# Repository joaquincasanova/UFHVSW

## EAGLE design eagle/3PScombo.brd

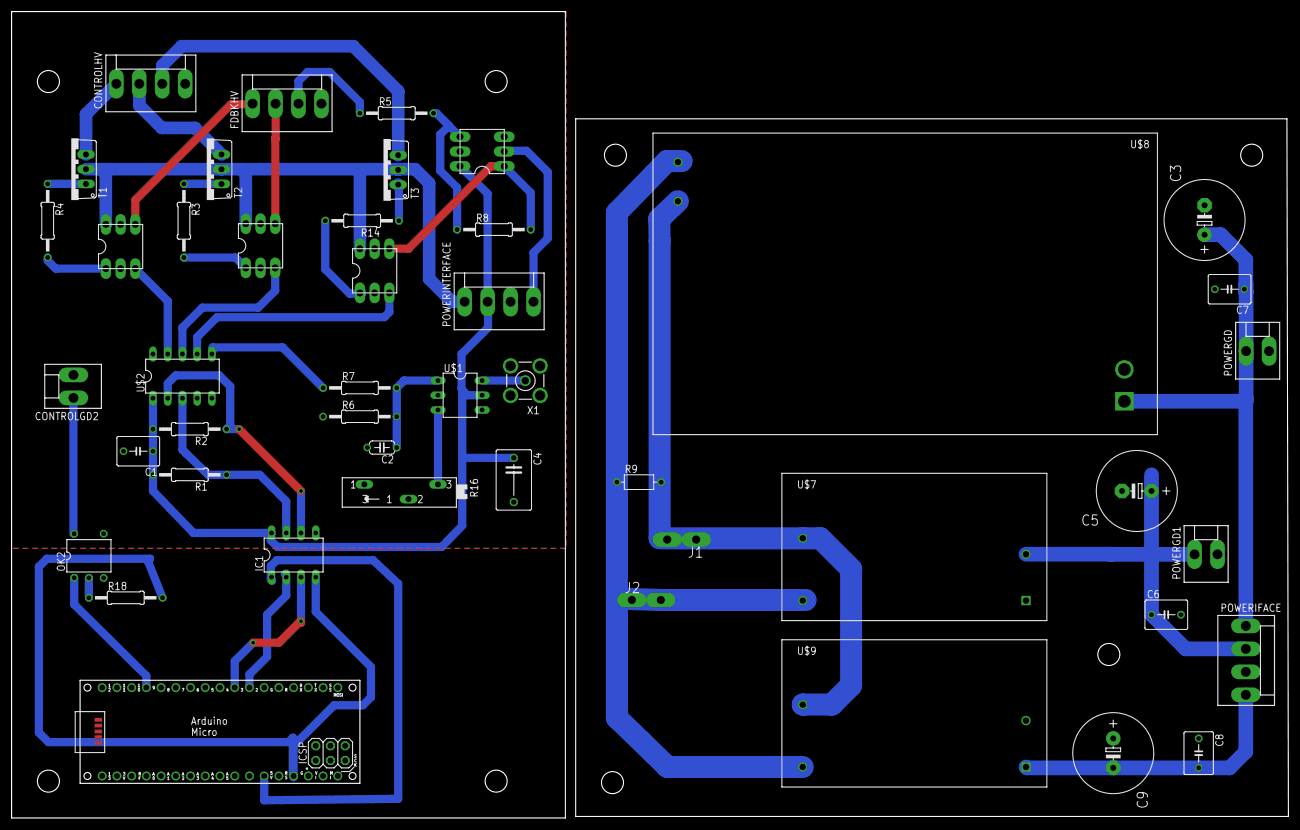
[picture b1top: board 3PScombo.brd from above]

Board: 2 copper layers, 220.2 x 139.1 mm, 46 parts (0 on the bottom side), 40 nets.

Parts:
C1, C6, C7, C8: C050-050X075
C2: 10n; C050-024X044
C3, C5, C9: E5-13
C4: C075-063X106
CONTROLGD2: KK-156-2
CONTROLHV: KK-156-4
FDBKHV: KK-156-4
IC1: ISO1540; DIL08
J1, J2: PIN2F061.100; F061.100
OK2: H11F1; DIL05
PCB1: ARDUINO_MICRO
POWERGD, POWERGD1: KK-156-2
POWERIFACE: KK-156-4
POWERINTERFACE: KK-156-4
R1, R2: 1.5k; 0207/12
R3, R4, R5, R8, R14: 1k; 0207/12
R6: 10k; 0207/12
R7: 40k; 0207/12
R9: VARISTOR-7,5; R-7,5
R16: SP19L
R18: 100; 0207/12
T1, T2, T3: TIP122V; TO220V
U$1: LTC6992; DIL06
U$2: MCP4728DIL; DIL10
U$3, U$4, U$5, U$6: OPA735DIL; DIL6
U$7, U$9: IRM-05-05
U$8: IRM-60-12
X1: BU-SMA-V

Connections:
+12V: POWERINTERFACE.1, T1.2, T2.2, T3.2, U$4.P$6, U$5.P$6, U$6.P$6
+12V1: C3.+, C7.1, POWERGD.1, POWERIFACE.1, U$8.P$1
-5V: POWERINTERFACE.4, U$3.P$2
-5V1: C8.2, C9.-, POWERIFACE.4, U$9.-V
A+5: IC1.1, PCB1.+5V
AGND: IC1.4, PCB1.GND., R18.2
ENSW2: CONTROLGD2.1, OK2.6
GND: C1.2, C2.2, C4.2, CONTROLGD2.2, CONTROLHV.4, FDBKHV.4, IC1.5, OK2.4, POWERINTERFACE.3, R6.1, R16.A, R16.S, U$1.DIV, U$1.GND, U$2.4, U$2.10, U$3.P$3, U$4.P$2, U$5.P$2, U$6.P$2, X1.2, X1.3, X1.4, X1.5
GND1: C3.-, C5.-, C6.2, C7.2, C8.1, C9.+, POWERGD.2, POWERGD1.2, POWERIFACE.3, U$7.-V, U$8.P$2, U$9.+V
unnamed: R7.1, U$2.6
unnamed: C2.1, R6.2, R7.2, U$1.MOD
unnamed: R4.1, T1.1
unnamed: CONTROLHV.1, T1.3
unnamed: CONTROLHV.3, T3.3
unnamed: FDBKHV.2, U$5.P$4
unnamed: OK2.2, R18.1
unnamed: FDBKHV.1, U$6.P$4
unnamed: FDBKHV.3, R5.1
unnamed: R3.2, U$5.P$1
unnamed: CONTROLHV.2, T2.3
unnamed: R16.E, U$1.SET
unnamed: U$1.OUT, X1.1
unnamed: R8.2, U$3.P$1, U$4.P$4
unnamed: R14.1, T3.1
unnamed: U$2.9, U$6.P$3
unnamed: U$2.8, U$5.P$3
unnamed: U$2.7, U$4.P$3
unnamed: R4.2, U$6.P$1
unnamed: R3.1, T2.1
unnamed: R14.2, U$4.P$1
unnamed: R5.2, R8.1, U$3.P$4
unnamed: J1.A1, J1.A2, R9.2, U$7.ACN, U$8.P$4, U$9.ACN
unnamed: J2.A1, J2.A2, R9.1, U$7.ACL, U$8.P$3, U$9.ACL
PWM9: OK2.1, PCB1.D9
SCL: IC1.3, PCB1.D3
SCL_OUT: IC1.6, R2.1, U$2.2
SDA: IC1.2, PCB1.D2
SDA_OUT: IC1.7, R1.1, U$2.3
VCC: C1.1, C4.1, IC1.8, POWERINTERFACE.2, R1.2, R2.2, U$1.VCC, U$2.1, U$3.P$6
VCC1: C5.+, C6.1, POWERGD1.1, POWERIFACE.2, U$7.+V

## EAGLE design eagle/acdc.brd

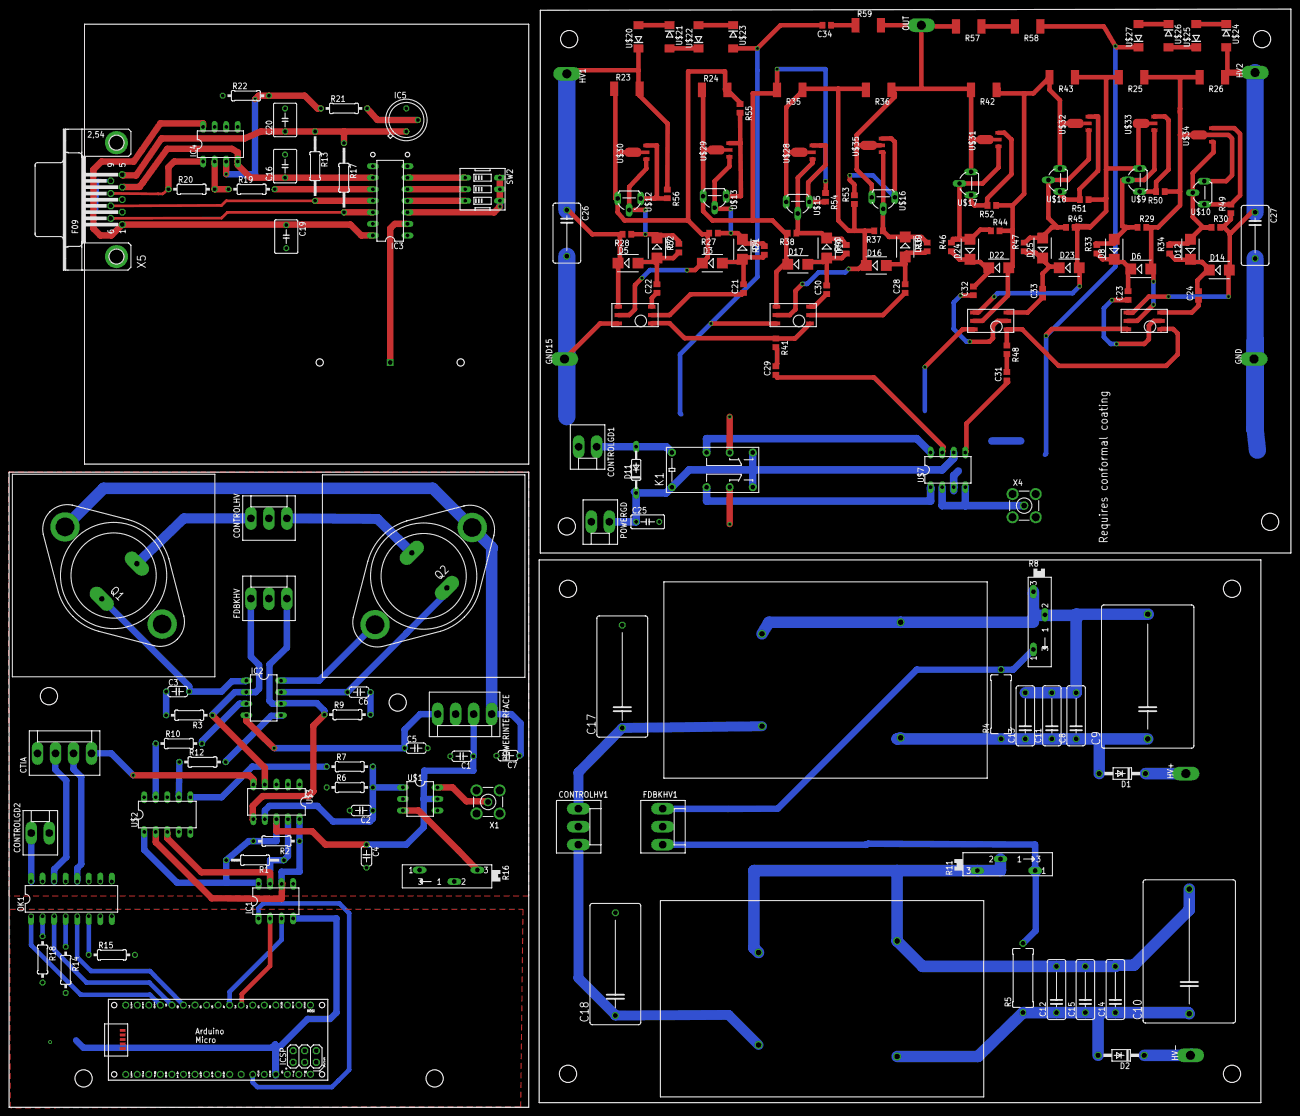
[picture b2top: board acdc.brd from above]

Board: 2 copper layers, 281.9 x 241.6 mm, 177 parts (1 on the bottom side), 122 nets.

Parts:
C1, C2, C3, C4, C5, C6, C7: 10n; C050-024X044
C8, C12: .01u; C102-043X133
C9, C10: 1u; C275-205X316
C11, C14: 1n; C102-043X133
C13, C15: 10p; C102-043X133
C16, C19, C20: 10n; C050-050X075
C17, C18: .1u; C225-113X268
C21, C22, C23, C24, C28, C29, C30, C31, C32, C33: 1u; C0805
C25: 10n; C050-030X075
C26, C27: 10p; C102-064X133
C34: 10n; C0805
CONTROLGD1, CONTROLGD2: KK-156-2
CONTROLHV, CONTROLHV1: KK-156-3
CTIA: KK-156-4
D1, D2: 1N4004; DO41-10
D3, D5, D6, D14, D16, D17, D22, D23: 1SMB5918BT3G; SMB
D4, D7, D8, D12, D18, D19, D24, D25: SMB
D11: 1N4148DO35-10; DO35-10
FDBKHV, FDBKHV1: KK-156-3
GND, GND15: TPPAD1-20Y; P1-20Y
HV1, HV2: TPPAD1-20Y; P1-20Y
HV+: TPPAD1-20Y; P1-20Y
HV-: TPPAD1-20Y; P1-20Y
IC1: ISO1540; DIL08
IC2, IC4: LT1352PA; DIL08
IC3: IVC102UADAPTOR; DIL14
IC5: AD580H; TO39
K1: G5V-2
OK1: PS2501"; DIL16
OUT: TPPAD1-20Y; P1-20Y
PCB1: ARDUINO_MICRO
POWERGD: KK-156-2
POWERINTERFACE: KK-156-4
Q1, Q2: 2N3055; TO3
R1: 10k; 0207/12
R2, R3, R6, R9, R10, R12, R19, R22: 10k; 0207/10
R4, R5: 2M; P0613/15
R7: 40k; 0207/10
R8, R11: SP19L
R13, R17: 10k; 0207/15
R14, R15, R18: 100; 0207/10
R16: 100k; SP19L
R20, R21: 1.5M; 0207/10
R23, R24, R25, R26, R35, R36, R42, R43, R57, R58, R59: 10M; R2512
R27, R28, R29, R30, R37, R38, R44, R45: 100k; R0805
R31, R32, R33, R34, R39, R40, R41, R46, R47, R48: 10; R0805
R49, R50, R51, R52: 6.67; R0805
R53, R54, R55, R56: 1.25; R0805
SW2: EDG-03
U$1: LTC6992; DIL06
U$2: MCP4728DIL; DIL10
U$3: ADS1015DIL; DIL10
U$4, U$5: EMCO-F104PIN; EMCO-F
U$6: CTIA
U$7: UCC27425; DIL08
U$8, U$11, U$14, U$19: DA-2320SMD6; SMD6
U$9, U$10, U$17, U$18: VN0550L; TO92L
U$12, U$13, U$15, U$16: VP0550L; TO92L
U$20, U$21, U$22, U$23, U$24, U$25, U$26, U$27: SMBJ170D-M3/H; DO214AA
U$28, U$29, U$30, U$35: VP2450; SOT89-BCE
U$31, U$32, U$33, U$34: VN2450; SOT89-BCE
X1, X4: BU-SMA-V
X5: F09HP

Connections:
+5V: C20.1, IC5.1, R13.1, R17.1, X5.5
+15V: C7.1, IC2.8, POWERINTERFACE.1, Q1.C, Q1.C/, Q2.C, Q2.C/
+15V1: C19.1, IC3.14, IC4.8, X5.1
+15V2: C25.1, D11.C, K1.1, K1.8, K1.9, POWERGD.1, U$7.6
-15V: C5.1, IC2.4, POWERINTERFACE.4
-15V1: C16.1, IC3.9, IC4.4, X5.4
A+5: IC1.1, PCB1.+5V
AGND: IC1.4, PCB1.GND., R14.2, R15.2, R18.2
CTIA: CTIA.4, U$3.5
D7: OK1.5, PCB1.D7
D8: OK1.3, PCB1.D8
ENSW: CONTROLGD1.1, D11.A, K1.16
ENSW2: CONTROLGD2.1, OK1.16
GND: C1.2, C2.2, C4.2, C5.2, C7.2, CONTROLGD2.2, CONTROLHV.2, CTIA.1, FDBKHV.2, IC1.5, OK1.11, OK1.13, OK1.15, POWERINTERFACE.3, R6.1, R16.A, R16.S, U$1.DIV, U$1.GND, U$2.4, U$2.10, U$3.1, U$3.3, X1.2, X1.3, X1.4, X1.5
GND1: C8.2, C9.2, C10.2, C11.2, C12.2, C13.2, C14.2, C15.2, C17.2, C18.2, CONTROLHV1.2, FDBKHV1.2, R8.E, R8.S, R11.E, R11.S, U$4.P$2, U$4.P$4, U$5.P$2, U$5.P$4
GND2: C16.2, C19.2, C20.2, IC3.1, IC3.13, IC5.3, R22.1, X5.2, X5.3, X5.9
GND3: C25.2, C26.2, C27.2, C34.2, CONTROLGD1.2, GND.TP, GND15.TP, K1.6, K1.11, POWERGD.2, R58.1, U$7.3, U$8.P$6, U$11.P$6, U$14.P$6, U$19.P$6, U$23.A, U$27.C, X4.2, X4.3, X4.4, X4.5
unnamed: R7.1, U$2.6
unnamed: OK1.4, R14.1
unnamed: C3.1, R3.2
unnamed: CONTROLHV.1, Q1.E
unnamed: CONTROLHV.3, Q2.E
unnamed: OK1.6, R15.1
unnamed: OK1.2, R18.1
unnamed: C8.1, C9.1, C11.1, C13.1, D1.A, R4.1, U$4.P$3
unnamed: C10.1, C12.1, C14.1, C15.1, D2.A, R5.1, U$5.P$3
unnamed: FDBKHV1.1, R4.2, R8.A
unnamed: FDBKHV1.3, R5.2, R11.A
unnamed: R16.E, U$1.SET
unnamed: U$1.OUT, X1.1
unnamed: D1.C, HV+.TP
unnamed: C17.1, CONTROLHV1.1, U$4.P$1
unnamed: IC2.3, R10.2
unnamed: C18.1, CONTROLHV1.3, U$5.P$1
unnamed: IC2.5, R12.2
unnamed: C3.2, IC2.1, Q1.B
unnamed: C6.1, R9.2
unnamed: C6.2, IC2.7, Q2.B
unnamed: D2.C, HV-.TP
unnamed: R10.1, U$2.9
unnamed: R12.1, U$2.7
unnamed: IC3.6, SW2.1
unnamed: IC3.5, SW2.2
unnamed: IC3.4, SW2.3
unnamed: IC3.3, SW2.4, SW2.5, SW2.6
unnamed: IC3.10, R19.2
unnamed: IC4.2, R19.1, R20.2
unnamed: IC4.3, R21.1, R22.2
unnamed: IC5.2, R21.2
unnamed: U$7.2, U$7.4, X4.1
unnamed: C29.1, U$7.7
unnamed: C31.1, U$7.5
unnamed: K1.4, U$7.1
unnamed: K1.13, U$7.8
unnamed: C21.1, U$8.P$2
unnamed: C22.1, U$8.P$3
unnamed: C23.1, U$11.P$2
unnamed: C24.1, U$11.P$3
unnamed: C23.2, D6.C, D8.C, R33.1
unnamed: C24.2, D12.C, D14.C, R34.1
unnamed: C22.2, D5.A, D7.A, R32.1
unnamed: C26.1, D5.C, HV1.TP, R23.2, R28.2, R56.1, U$8.P$4, U$20.C
unnamed: D6.A, R25.1, R26.2, R29.2, R50.1, U$10.1, U$11.P$5, U$34.C, U$34.C@1
unnamed: D3.C, R23.1, R24.2, R27.2, R55.1, U$8.P$5, U$12.1, U$30.C, U$30.C@1
unnamed: D4.C, R27.1, R31.2, U$13.2, U$29.B
unnamed: C21.2, D3.A, D4.A, R31.1
unnamed: D12.A, R30.1, R34.2, U$10.2, U$34.B
unnamed: D7.C, R28.1, R32.2, U$12.2, U$30.B
unnamed: C27.1, D14.A, HV2.TP, R26.1, R30.2, R49.1, U$11.P$4, U$24.A
unnamed: C28.1, U$14.P$2
unnamed: C30.1, U$14.P$3
unnamed: C30.2, D17.A, D19.A, R40.1
unnamed: D16.C, R35.1, R36.2, R37.2, R53.1, U$14.P$5, U$15.1, U$28.C, U$28.C@1
unnamed: D18.C, R37.1, R39.2, U$16.2, U$35.B
unnamed: C28.2, D16.A, D18.A, R39.1
unnamed: D19.C, R38.1, R40.2, U$15.2, U$28.B
unnamed: R41.1, U$8.P$1, U$14.P$1
unnamed: C29.2, R41.2
unnamed: C32.1, U$19.P$2
unnamed: C33.1, U$19.P$3
unnamed: C32.2, D22.C, D24.C, R46.1
unnamed: C33.2, D23.C, D25.C, R47.1
unnamed: D22.A, R42.1, R43.2, R44.2, R52.1, U$18.1, U$19.P$5, U$32.C, U$32.C@1
unnamed: D25.A, R45.1, R47.2, U$18.2, U$32.B
unnamed: R48.1, U$11.P$1, U$19.P$1
unnamed: C31.2, R48.2
unnamed: D24.A, R44.1, R46.2, U$17.2, U$31.B
unnamed: D23.A, R25.2, R43.1, R45.2, R51.1, U$9.1, U$19.P$4, U$33.C, U$33.C@1
unnamed: OUT.TP, R36.1, R42.2, R57.2, R59.2, U$16.1, U$17.1, U$31.C, U$31.C@1, U$35.C, U$35.C@1
unnamed: D17.C, R24.1, R35.2, R38.2, R54.1, U$13.1, U$14.P$4, U$29.C, U$29.C@1
unnamed: R49.2, U$10.3, U$34.E
unnamed: R50.2, U$9.3, U$33.E
unnamed: R51.2, U$18.3, U$32.E
unnamed: R52.2, U$17.3, U$31.E
unnamed: R56.2, U$12.3, U$30.E
unnamed: R55.2, U$13.3, U$29.E
unnamed: R53.2, U$16.3, U$35.E
unnamed: R54.2, U$15.3, U$28.E
unnamed: R57.1, R58.2
unnamed: C34.1, R59.1
unnamed: U$20.A, U$21.C
unnamed: U$21.A, U$22.C
unnamed: U$22.A, U$23.C
unnamed: U$24.C, U$25.A
unnamed: U$25.C, U$26.A
unnamed: U$26.C, U$27.A
unnamed: D8.A, R29.1, R33.2, U$9.2, U$33.B
PWM9: OK1.1, PCB1.D9
RDBK1: FDBKHV.1, IC2.2, R3.1, U$3.4
RDBK3: FDBKHV.3, IC2.6, R9.1, U$3.6
RDBK4: C2.1, R6.2, R7.2, U$1.MOD, U$3.7
RESET: CTIA.3, OK1.12
RESET1: IC3.12, R17.2, X5.6
SAMPLE: CTIA.2, OK1.14
SAMPLE1: IC3.11, R13.2, X5.7
SCL: IC1.3, PCB1.D3
SCL_OUT: IC1.6, R2.1, U$2.2, U$3.10
SDA: IC1.2, PCB1.D2
SDA_OUT: IC1.7, R1.1, U$2.3, U$3.9
VCC: C1.1, C4.1, IC1.8, POWERINTERFACE.2, R1.2, R2.2, U$1.VCC, U$2.1, U$3.8
VIN: IC3.2, U$6.P$1
VOUT: IC4.1, R20.1, X5.8

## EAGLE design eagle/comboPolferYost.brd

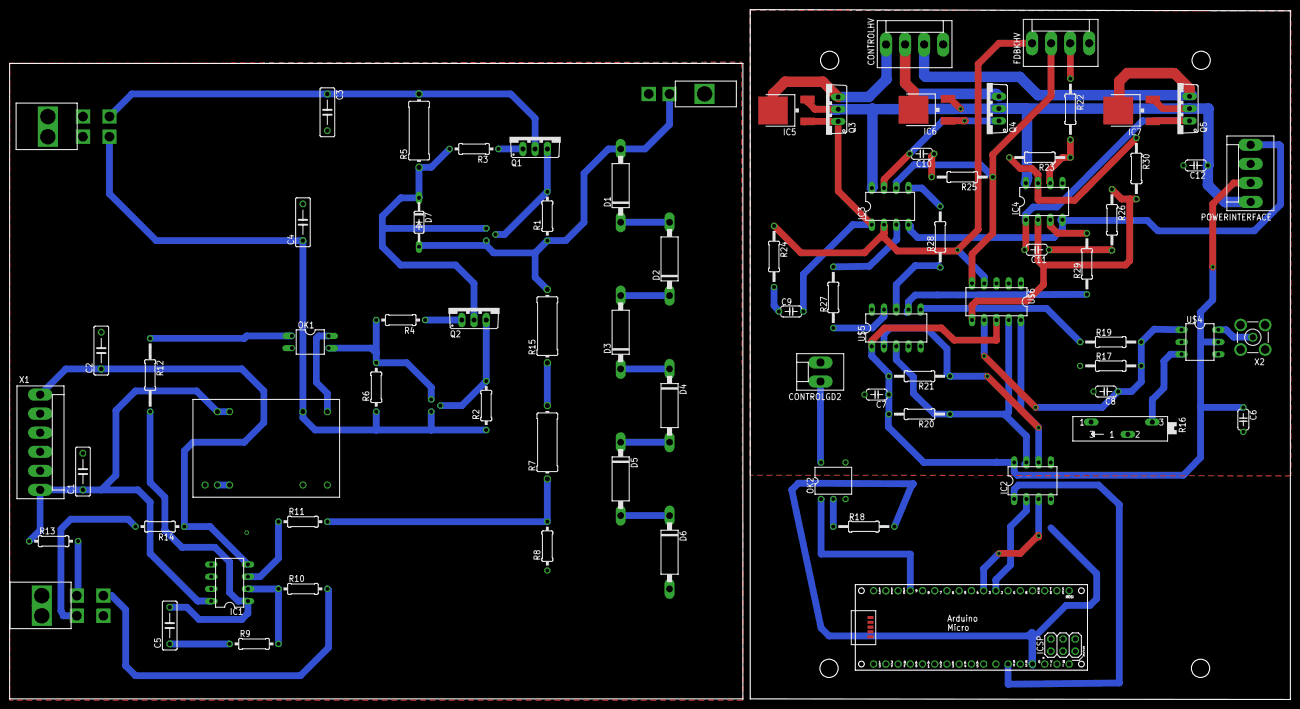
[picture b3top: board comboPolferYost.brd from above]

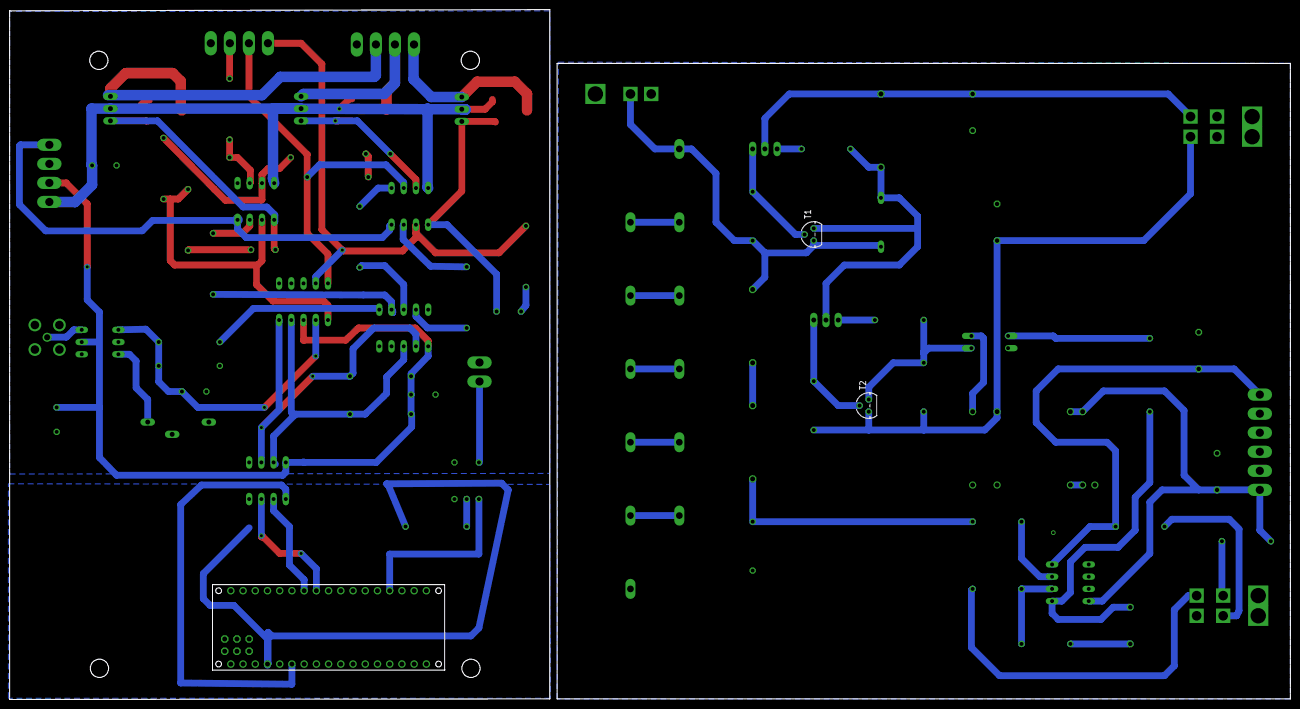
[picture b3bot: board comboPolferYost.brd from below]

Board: 2 copper layers, 266.2 x 143.4 mm, 79 parts (2 on the bottom side), 67 nets.

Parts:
C1, C2, C3, C4, C5: 10n; C075-032X103
C6, C7, C8, C9, C10, C11, C12: 10n; C050-024X044
CONTROLGD2: KK-156-2
CONTROLHV: KK-156-4
D1, D2, D3, D4, D5, D6: P6KEXX; CB417-15
D7: 1N4148DO35-10; DO35-10
DC1: NCS
FDBKHV: KK-156-4
IC1, IC3, IC4: LT1352PA; DIL08
IC2: ISO1540; DIL08
IC5, IC6, IC7: LM317MABDT; DPACK
OK1: PC817; DIL04
OK2: H11F1; DIL05
PCB1: ARDUINO_MICRO
POWERINTERFACE: KK-156-4
Q1, Q2: TO220BV
Q3, Q4, Q5: TIP122V; TO220V
R1, R2: 65; 0207/10
R3, R4: 100; 0207/10
R5, R7, R15: 1M; 0414/15
R6: 100k; 0207/10
R8: 50k; 0207/10
R9, R10, R11: 10k; 0207/10
R12: 250; 0207/15
R13, R14: 20k; 0207/10
R16: 100k; SP19L
R17, R24, R25, R26, R27, R28, R29, R30: 10k; 0207/12
R18: 100; 0207/12
R19: 40k; 0207/12
R20, R21: 1.5k; 0207/12
R22, R23: 20k; 0207/12
T1, T2: 2N3904; TO92
U$1, U$2: 5569-4; 5669-4
U$3: 5569-2
U$4: LTC6992; DIL06
U$5: MCP4728DIL; DIL10
U$6: ADS1015DIL; DIL10
X1: KK-156-6
X2: BU-SMA-V

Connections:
+5V: X1.4, X1.5
+12V: C12.1, IC3.8, IC4.8, IC5.3, IC6.3, IC7.3, POWERINTERFACE.1, Q3.2, Q4.2, Q5.2
+15V: C1.1, DC1.P$8, DC1.P$9, IC1.8, R13.1, X1.6
-5V: IC3.4, IC4.4, POWERINTERFACE.4
-15V: C2.1, IC1.4, R14.1, X1.1
A+5: IC2.1, PCB1.+5V
AGND: IC2.4, PCB1.GND., R18.2
ENSW2: CONTROLGD2.1, OK2.6
GND: C1.2, C2.2, C3.2, C4.2, D6.A, DC1.P$2, DC1.P$3, OK1.2, R8.1, U$2.P$1, U$2.P$2, U$3.P$2, X1.2, X1.3
GND1: C6.2, C7.2, C8.2, C12.2, CONTROLGD2.2, CONTROLHV.4, FDBKHV.4, IC2.5, IC4.5, OK2.4, POWERINTERFACE.3, R16.A, R16.S, R17.1, U$4.DIV, U$4.GND, U$5.4, U$5.10, U$6.1, U$6.3, X2.2, X2.3, X2.4, X2.5
unnamed: D1.C, D2.A
unnamed: D2.C, D3.A
unnamed: D3.C, D4.C
unnamed: D4.A, D5.C
unnamed: D5.A, D6.C
unnamed: Q1.G, R3.1
unnamed: D7.C, Q2.D, R3.2, R5.1, T1.1
unnamed: Q1.S, R1.2, T1.2
unnamed: R13.2, U$1.P$2
unnamed: D1.A, D7.A, R1.1, R15.2, T1.3, U$3.P$1
unnamed: Q2.G, R4.1
unnamed: OK1.3, R4.2, R6.2, T2.1
unnamed: R10.2, U$1.P$4
unnamed: Q2.S, R2.2, T2.2
unnamed: DC1.P$6, OK1.4
unnamed: C5.1, R9.1
unnamed: IC1.2, R9.2, R10.1
unnamed: C5.2, IC1.1, R12.2
unnamed: IC1.3, R11.1
unnamed: R7.1, R8.2, R11.2
unnamed: R16.E, U$4.SET
unnamed: R7.2, R15.1
unnamed: R14.2, U$1.P$1
unnamed: OK1.1, R12.1
unnamed: U$4.OUT, X2.1
unnamed: IC4.7, R23.2, R30.1
unnamed: IC3.5, R28.2
unnamed: IC4.3, R29.2
unnamed: R19.1, U$5.6
unnamed: C9.2, IC3.1, IC5.1, Q3.1
unnamed: CONTROLHV.1, IC5.4, Q3.3
unnamed: C10.2, IC3.7, IC6.1, Q4.1
unnamed: FDBKHV.3, R22.1
unnamed: IC4.6, R22.2, R23.1
unnamed: C11.2, IC4.1, IC7.1, Q5.1
unnamed: OK2.2, R18.1
unnamed: C9.1, R24.2
unnamed: C10.1, R25.2
unnamed: C11.1, R26.2
unnamed: IC3.3, R27.2
unnamed: R27.1, U$5.9
unnamed: R29.1, U$5.7
unnamed: R28.1, U$5.8
unnamed: CONTROLHV.3, IC7.4, Q5.3
unnamed: CONTROLHV.2, IC6.4, Q4.3
PWM9: OK2.1, PCB1.D9
RDBK1: FDBKHV.1, IC3.2, R24.1, U$6.4
RDBK2: FDBKHV.2, IC3.6, R25.1, U$6.5
RDBK3: IC4.2, R26.1, R30.2, U$6.6
RDBK4: C8.1, R17.2, R19.2, U$4.MOD, U$6.7
SCL: IC2.3, PCB1.D3
SCL_OUT: IC2.6, R21.1, U$5.2, U$6.10
SDA: IC2.2, PCB1.D2
SDA_OUT: IC2.7, R20.1, U$5.3, U$6.9
V+: C3.1, Q1.D, R5.2, U$2.P$4
V-: C4.1, DC1.P$7, R2.1, R6.1, T2.3, U$2.P$3
VCC: C6.1, C7.1, IC2.8, POWERINTERFACE.2, R20.2, R21.2, U$4.VCC, U$5.1, U$6.8

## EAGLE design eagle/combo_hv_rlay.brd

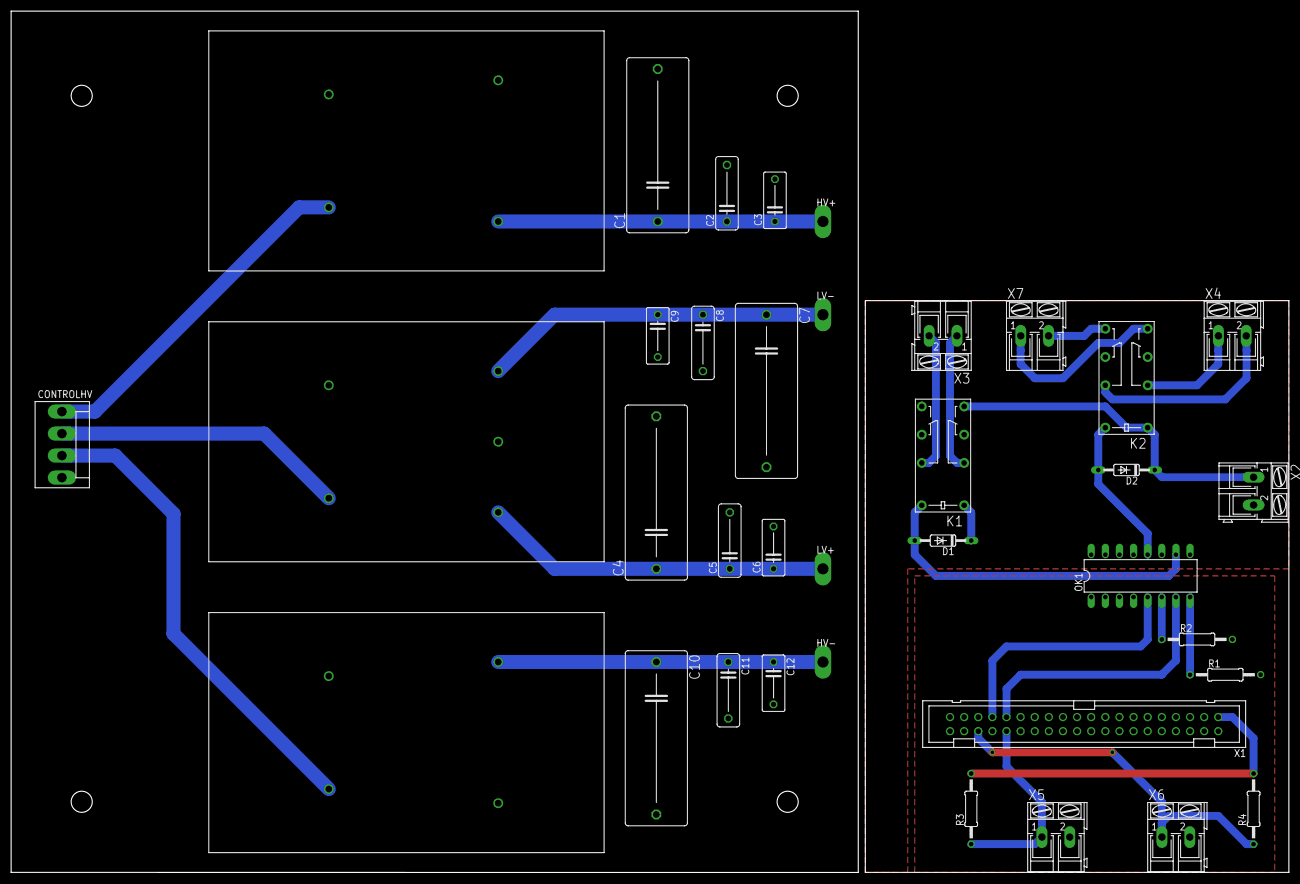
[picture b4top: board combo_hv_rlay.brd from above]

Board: 2 copper layers, 229.9 x 155.0 mm, 36 parts (0 on the bottom side), 28 nets.

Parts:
C1, C4, C7, C10: 1u; C275-113X316
C2, C5, C8, C11: .1u; C102-043X133
C3, C6, C9, C12: .01u; C075-042X103
CONTROLHV: KK-156-4
D1, D2: 1N4148DO35-10; DO35-10
HV+: TPPAD1-20Y; P1-20Y
HV-: TPPAD1-20Y; P1-20Y
K1, K2: G5V-2
LV+: TPPAD1-20Y; P1-20Y
LV-: TPPAD1-20Y; P1-20Y
OK1: PS2501"; DIL16
R1, R2: 200; 0207/12
R3, R4: 1k; 0207/12
U$1, U$3: EMCO-F104PIN; EMCO-F
U$2: EMCO-F20CT; EMCO-F*CT
X1: 2540-; PAK100/2500-40
X2, X3, X4, X5, X6, X7: AK300/2

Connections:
+3V3: R3.2, R4.2, X1.1, X1.17
+5V: X1.2, X1.4
+24V: D1.C, D2.C, K1.1, K1.8, K2.1, X2.1
GND: C1.2, C2.2, C3.2, C4.2, C5.2, C6.2, C7.2, C8.2, C9.2, C10.2, C11.2, C12.2, CONTROLHV.4, U$1.P$2, U$1.P$4, U$2.P$2, U$2.P$5, U$3.P$2, U$3.P$3
GND1: R1.2, R2.2, X1.6, X1.9, X1.14, X1.20, X1.25, X1.30, X1.34, X1.39, X5.2, X6.2
GND2: K1.9, OK1.9, OK1.11, X2.2
GPIO6: OK1.7, X1.31
GPIO13: OK1.5, X1.33
unnamed: C1.1, C2.1, C3.1, HV+.TP, U$1.P$3
unnamed: C10.1, C11.1, C12.1, HV-.TP, U$3.P$4
unnamed: OK1.8, R1.1
unnamed: OK1.6, R2.1
unnamed: C4.1, C5.1, C6.1, LV+.TP, U$2.P$3
unnamed: C7.1, C8.1, C9.1, LV-.TP, U$2.P$4
unnamed: R3.1, X1.32, X5.1
unnamed: D1.A, K1.16, OK1.10
unnamed: D2.A, K2.16, OK1.12
unnamed: K1.4, X3.1
unnamed: K1.13, X3.2
unnamed: X1.36, X6.1
unnamed: R4.1, X6.1
unnamed: K2.13, X4.2
unnamed: K2.4, X4.1
unnamed: K2.8, X7.1
unnamed: K2.9, X7.2
VREG1: CONTROLHV.1, U$1.P$1
VREG2: CONTROLHV.2, U$2.P$1
VREG3: CONTROLHV.3, U$3.P$1

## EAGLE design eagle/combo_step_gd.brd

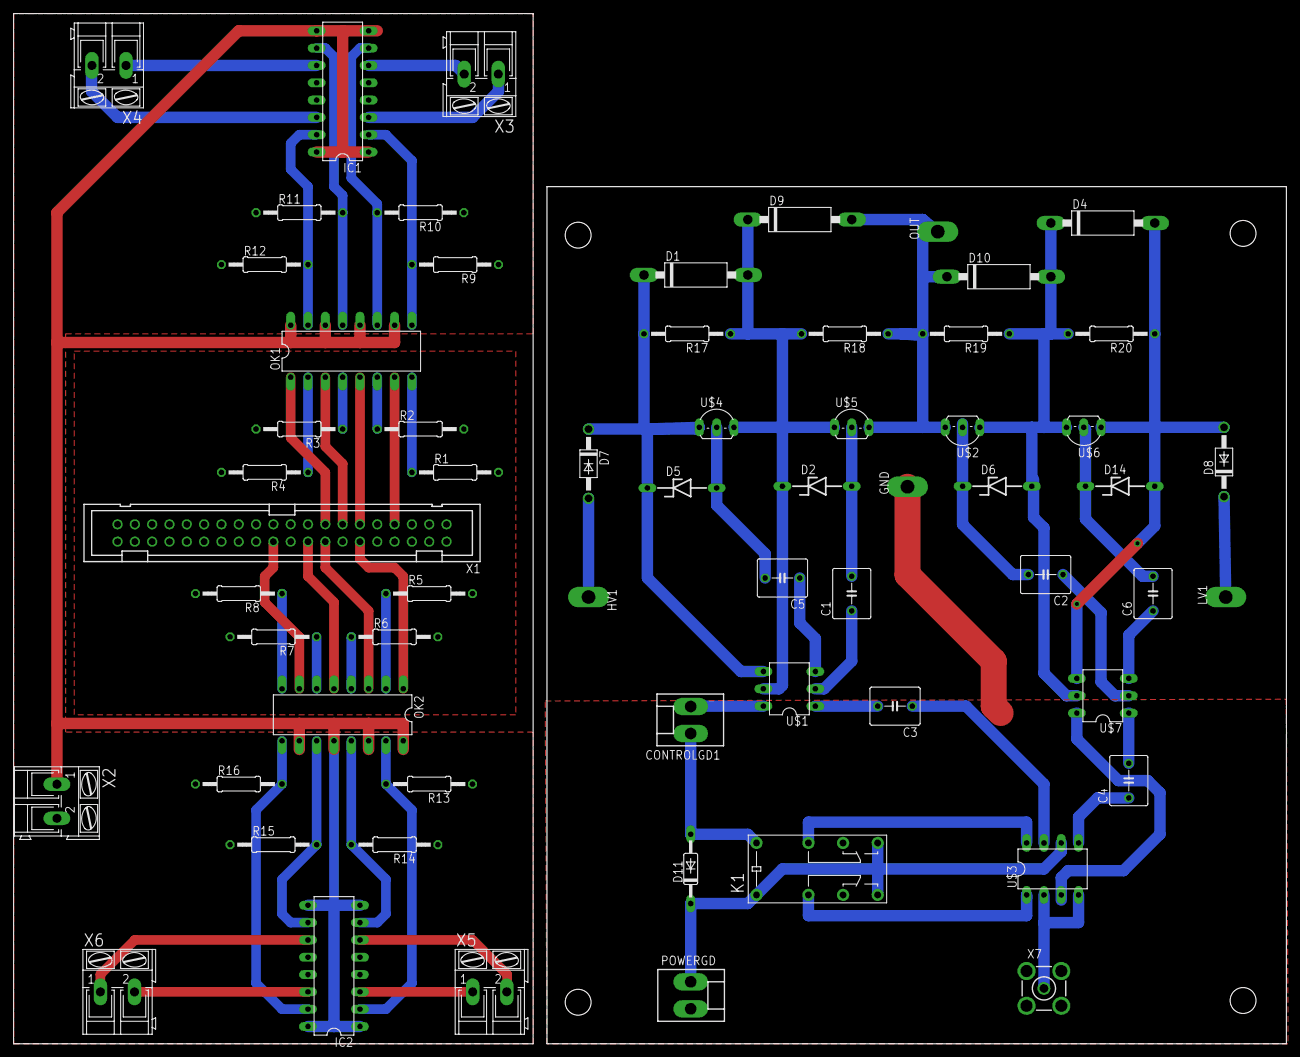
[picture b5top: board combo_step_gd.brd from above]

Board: 2 copper layers, 186.7 x 151.1 mm, 62 parts (0 on the bottom side), 62 nets.

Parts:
C1, C2, C3, C4, C5, C6: C050-055X075
CONTROLGD1: KK-156-2
D1, D4, D9, D10: P6KEXXA; C1702-15
D2, D5, D6, D14: 4735; ZDIO-10
D7, D8: 1N4004; DO41-10
D11: 1N4148DO35-10; DO35-10
GND: TPPAD1-20Y; P1-20Y
HV1: TPPAD1-20Y; P1-20Y
IC1, IC2: L293D; DIL16
K1: G5V-2
LV1: TPPAD1-20Y; P1-20Y
OK1, OK2: PS2501"; DIL16
OUT: TPPAD1-20Y; P1-20Y
POWERGD: KK-156-2
R1, R2, R3, R4, R5, R6, R7, R8: 200; 0207/12
R9, R10, R11, R12, R13, R14, R15, R16: 10K; 0207/12
R17, R18, R19, R20: 1M; 0207/12
U$1, U$7: DA-2320; DIL06
U$2, U$6: VN0550; TO92-
U$3: UCC27425; DIL08
U$4, U$5: VP0550; TO92-
X1: 2540-; PAK100/2500-40
X2, X3, X4, X5, X6: AK300/2
X7: BU-SMA-V

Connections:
+3V3: X1.1, X1.17
+5V: X1.2, X1.4
+15V: D11.C, K1.1, K1.8, K1.9, POWERGD.1, U$3.6
ENSW: CONTROLGD1.1, D11.A, K1.16
GND: R1.2, R2.2, R3.2, R4.2, R5.2, R6.2, R7.2, R8.2, X1.6, X1.9, X1.14, X1.20, X1.25, X1.30, X1.34, X1.39
GND1: IC1.4, IC1.5, IC1.12, IC1.13, IC2.4, IC2.5, IC2.12, IC2.13, R9.1, R10.1, R11.1, R12.1, R13.1, R14.1, R15.1, R16.1, X2.2
GND2: CONTROLGD1.2, GND.TP, K1.6, K1.11, POWERGD.2, U$1.6, U$3.3, U$7.6, X7.2, X7.3, X7.4, X7.5
unnamed: OK1.8, R1.1
unnamed: OK1.6, R2.1
unnamed: OK1.4, R3.1
unnamed: OK1.2, R4.1
unnamed: OK2.2, R5.1
unnamed: OK2.4, R6.1
unnamed: OK2.6, R7.1
unnamed: OK2.8, R8.1
unnamed: IC1.2, OK1.9, R9.2
unnamed: IC1.7, OK1.11, R10.2
unnamed: IC1.10, OK1.13, R11.2
unnamed: IC1.15, OK1.15, R12.2
unnamed: IC2.2, OK2.15, R13.2
unnamed: IC2.7, OK2.13, R14.2
unnamed: IC2.10, OK2.11, R15.2
unnamed: IC2.15, OK2.9, R16.2
unnamed: IC1.3, X3.1
unnamed: IC1.6, X3.2
unnamed: IC1.14, X4.2
unnamed: IC1.11, X4.1
unnamed: IC2.3, X5.1
unnamed: IC2.6, X5.2
unnamed: IC2.11, X6.1
unnamed: IC2.14, X6.2
unnamed: OK1.1, X1.15
unnamed: OK2.1, X1.12
unnamed: OK2.3, X1.16
unnamed: OK2.5, X1.18
unnamed: OK2.7, X1.22
unnamed: OK1.3, X1.13
unnamed: OK1.5, X1.11
unnamed: OK1.7, X1.7
unnamed: U$3.2, U$3.4, X7.1
unnamed: C3.2, U$1.1
unnamed: C3.1, U$3.7
unnamed: C4.1, U$3.5
unnamed: K1.4, U$3.1
unnamed: K1.13, U$3.8
unnamed: C1.1, U$1.2
unnamed: C5.1, U$1.3
unnamed: C2.1, U$7.2
unnamed: C6.1, U$7.3
unnamed: C2.2, D6.C, U$2.2
unnamed: C6.2, D14.C, U$6.2
unnamed: C1.2, D2.A, U$5.2
unnamed: C5.2, D5.A, U$4.2
unnamed: D9.A, D10.C, OUT.TP, R18.1, R19.2, U$2.1, U$5.1
unnamed: D1.C, D5.C, D7.C, R17.2, U$1.4, U$4.3
unnamed: D1.A, D2.C, D9.C, R17.1, R18.2, U$1.5, U$4.1, U$5.3
unnamed: D7.A, HV1.TP
unnamed: C4.2, U$7.1
unnamed: D8.C, LV1.TP
unnamed: D4.C, D6.A, D10.A, R19.1, R20.2, U$2.3, U$6.1
unnamed: D4.A, D8.A, D14.A, R20.1, U$6.3, U$7.4
VCC: IC1.1, IC1.8, IC1.9, IC1.16, IC2.1, IC2.8, IC2.9, IC2.16, OK1.10, OK1.12, OK1.14, OK1.16, OK2.10, OK2.12, OK2.14, OK2.16, X2.1

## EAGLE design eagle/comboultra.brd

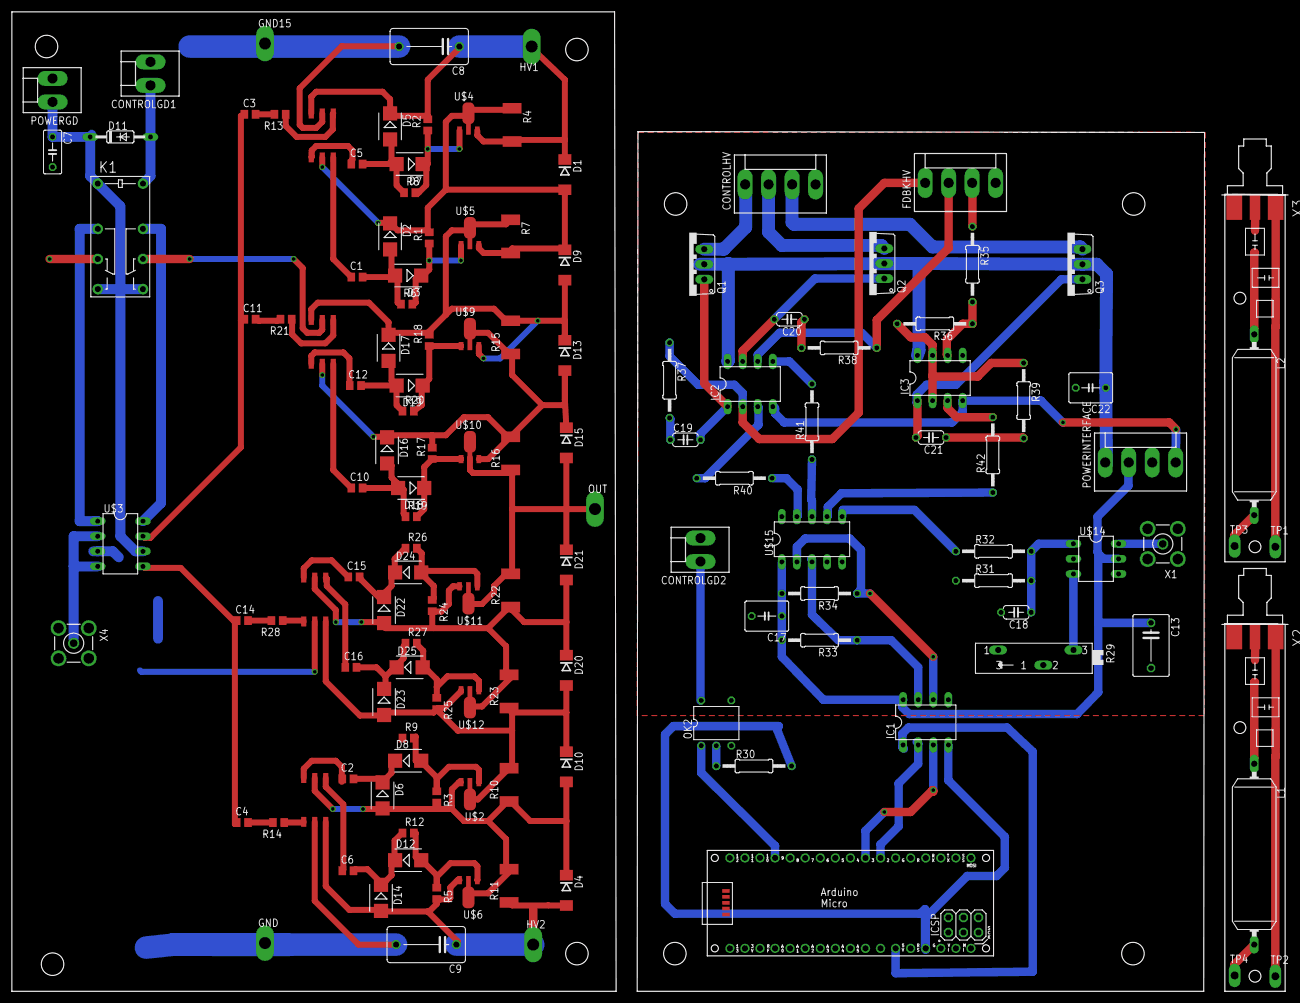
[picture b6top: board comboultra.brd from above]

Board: 2 copper layers, 215.1 x 165.1 mm, 140 parts (0 on the bottom side), 94 nets.

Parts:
C1, C2, C3, C4, C5, C6, C10, C11, C12, C14, C15, C16: .22u; C0805
C7: C050-030X075
C8, C9: 10p; C102-064X133
C13: C075-063X106
C17, C22: C050-050X075
C18: 10n; C050-024X044
C19, C20, C21: C050-024X044
C23, C26: 5-20; SGC3S
C24, C27: 10-30; SGC3S
C25, C28: 100p; 1111
CONTROLGD1, CONTROLGD2: KK-156-2
CONTROLHV: KK-156-4
D1, D4, D9, D10, D13, D15, D20, D21: SMBJ170D-M3/H; DO214AA
D2, D5, D6, D14, D16, D17, D22, D23: 4742; SMB
D3, D7, D8, D12, D18, D19, D24, D25: SMB
D11: 1N4148DO35-10; DO35-10
FDBKHV: 40k; KK-156-4
GND, GND15: TPPAD1-20Y; P1-20Y
HV1, HV2: TPPAD1-20Y; P1-20Y
IC1: ISO1540; DIL08
IC2, IC3: LT1352PA; DIL08
K1: G5V-2
L1, L2: B82111; SUKW1-30
OK2: H11F1; DIL05
OUT: TPPAD1-20Y; P1-20Y
PCB1: ARDUINO_MICRO
POWERGD: KK-156-2
POWERINTERFACE: KK-156-4
Q1, Q2, Q3: TIP122V; TO220V
R1, R2, R3, R5, R17, R18, R24, R25: 100k; R0805
R4, R7, R10, R11, R15, R16, R22, R23: 1M; R2512
R6, R8, R9, R12, R19, R20, R26, R27: 10; R0805
R13, R14, R21, R28: 50; R0805
R29: SP19L
R30: 100; 0207/12
R31: 10k; 0207/12
R32: 40k; 0207/12
R33, R34: 1.5k; 0207/12
R35, R36, R40, R41: 20k; 0207/12
R37, R38, R39: 0207/12
R42: 12; 0207/12
TP1, TP2, TP3, TP4: TPPAD1-13Y; P1-13Y
U$1, U$7, U$8, U$13: DA-2320SMD6; SMD6
U$2, U$6, U$11, U$12: VN2450; SOT89-BCE
U$3: UCC27425; DIL08
U$4, U$5, U$9, U$10: VP2450; SOT89-BCE
U$14: LTC6992; DIL06
U$15: MCP4728DIL; DIL10
X1, X4: BU-SMA-V
X2, X3: SMA-142-0711-821/826; J502-ND-142-0711-821/826

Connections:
+12V: C22.1, IC2.8, IC3.8, POWERINTERFACE.1, Q1.2, Q2.2, Q3.2
+15V: C7.1, D11.C, K1.1, K1.8, K1.9, POWERGD.1, U$3.6
-5V: IC2.4, IC3.4, POWERINTERFACE.4
A+5: IC1.1, PCB1.+5V
AGND: IC1.4, PCB1.GND., R30.2
ENSW: CONTROLGD1.1, D11.A, K1.16
ENSW2: CONTROLGD2.1, OK2.6
GND: C7.2, C8.2, C9.2, CONTROLGD1.2, GND.TP, GND15.TP, K1.6, K1.11, POWERGD.2, U$1.P$2, U$3.3, U$7.P$2, U$8.P$2, U$13.P$2, X4.2, X4.3, X4.4, X4.5
GND1: C13.2, C17.2, C18.2, C22.2, CONTROLGD2.2, CONTROLHV.4, FDBKHV.4, IC1.5, IC3.5, OK2.4, POWERINTERFACE.3, R29.A, R29.S, R31.1, U$14.DIV, U$14.GND, U$15.4, U$15.10, X1.2, X1.3, X1.4, X1.5
unnamed: U$3.2, U$3.4, X4.1
unnamed: C3.1, C11.1, U$3.7
unnamed: R13.1, U$1.P$1
unnamed: C4.1, C14.1, U$3.5
unnamed: C1.1, U$1.P$6
unnamed: R14.1, U$7.P$1
unnamed: C5.1, U$1.P$4
unnamed: D3.C, R1.1, R6.2, U$5.B
unnamed: R29.E, U$14.SET
unnamed: C1.2, D2.A, D3.A, R6.1
unnamed: D12.A, R5.1, R12.2, U$6.B
unnamed: D7.C, R2.1, R8.2, U$4.B
unnamed: D4.C, D6.A, D10.A, R3.2, R10.1, R11.2, U$2.E, U$6.C, U$6.C@1, U$7.P$5
unnamed: K1.4, U$3.1
unnamed: K1.13, U$3.8
unnamed: C5.2, D5.A, D7.A, R8.1
unnamed: C8.1, D1.C, D5.C, HV1.TP, R2.2, R4.2, U$1.P$3, U$4.E
unnamed: D1.A, D2.C, D9.C, R1.2, R4.1, R7.2, U$1.P$5, U$4.C, U$4.C@1, U$5.E
unnamed: C3.2, R13.2
unnamed: C4.2, R14.2
unnamed: U$14.OUT, X1.1
unnamed: C2.1, U$7.P$6
unnamed: C6.1, U$7.P$4
unnamed: C9.1, D4.A, D14.A, HV2.TP, R5.2, R11.1, U$6.E, U$7.P$3
unnamed: C2.2, D6.C, D8.C, R9.1
unnamed: D15.A, D21.C, OUT.TP, R16.1, R22.2, U$10.C, U$10.C@1, U$11.C, U$11.C@1
unnamed: C6.2, D12.C, D14.C, R12.1
unnamed: C10.1, U$8.P$6
unnamed: C12.1, U$8.P$4
unnamed: C12.2, D17.A, D19.A, R20.1
unnamed: C18.1, R31.2, R32.2, U$14.MOD
unnamed: D9.A, D13.C, D17.C, R7.1, R15.2, R18.2, U$5.C, U$5.C@1, U$8.P$3, U$9.E
unnamed: D13.A, D15.C, D16.C, R15.1, R16.2, R17.2, U$8.P$5, U$9.C, U$9.C@1, U$10.E
unnamed: D18.C, R17.1, R19.2, U$10.B
unnamed: C10.2, D16.A, D18.A, R19.1
unnamed: D19.C, R18.1, R20.2, U$9.B
unnamed: R21.1, U$8.P$1
unnamed: C11.2, R21.2
unnamed: FDBKHV.1, IC2.2, R37.1
unnamed: C15.1, U$13.P$6
unnamed: C16.1, U$13.P$4
unnamed: C15.2, D22.C, D24.C, R26.1
unnamed: C16.2, D23.C, D25.C, R27.1
unnamed: IC3.2, IC3.7, R36.2, R39.1
unnamed: IC2.5, R41.2
unnamed: D20.C, D21.A, D22.A, R22.1, R23.2, R24.2, U$11.E, U$12.C, U$12.C@1, U$13.P$5
unnamed: D25.A, R25.1, R27.2, U$12.B
unnamed: R28.1, U$13.P$1
unnamed: C14.2, R28.2
unnamed: D24.A, R24.1, R26.2, U$11.B
unnamed: D10.C, D20.A, D23.A, R10.2, R23.1, R25.2, U$2.C, U$2.C@1, U$12.E, U$13.P$3
unnamed: IC3.3, R42.2
unnamed: R32.1, U$15.6
unnamed: C19.2, IC2.1, Q1.1
unnamed: CONTROLHV.1, Q1.3
unnamed: FDBKHV.2, IC2.6, R38.1
unnamed: C20.2, IC2.7, Q2.1
unnamed: FDBKHV.3, R35.1
unnamed: IC3.6, R35.2, R36.1
unnamed: C21.2, IC3.1, Q3.1
unnamed: OK2.2, R30.1
unnamed: C19.1, R37.2
unnamed: C20.1, R38.2
unnamed: C21.1, R39.2
unnamed: IC2.3, R40.2
unnamed: R40.1, U$15.9
unnamed: R42.1, U$15.7
unnamed: R41.1, U$15.8
unnamed: CONTROLHV.3, Q3.3
unnamed: CONTROLHV.2, Q2.3
unnamed: C23.P$1, C24.P$2, C25.P$1, L1.1
unnamed: C23.P$2, X2.1
unnamed: C24.P$1, C25.P$2, TP2.TP, X2.G@1, X2.G@2, X2.G@3, X2.G@4
unnamed: L1.2, TP4.TP
unnamed: C26.P$1, C27.P$2, C28.P$1, L2.1
unnamed: C26.P$2, X3.1
unnamed: C27.P$1, C28.P$2, TP1.TP, X3.G@1, X3.G@2, X3.G@3, X3.G@4
unnamed: L2.2, TP3.TP
unnamed: D8.A, R3.1, R9.2, U$2.B
PWM9: OK2.1, PCB1.D9
SCL: IC1.3, PCB1.D3
SCL_OUT: IC1.6, R34.1, U$15.2
SDA: IC1.2, PCB1.D2
SDA_OUT: IC1.7, R33.1, U$15.3
VCC: C13.1, C17.1, IC1.8, POWERINTERFACE.2, R33.2, R34.2, U$14.VCC, U$15.1
